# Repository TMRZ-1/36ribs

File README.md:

# 36ribs

Here you will find everything you need to make your own 36ribs keyboard. It's my first project, so it's not too complicated. 

# UPDATE
Added one led under controller to light it a bit in the middle and updated vial software. Added two new cases, with magnets, normal one just without screws in case and second one with integrated plate that need only magnets. From these three my fav is one that have top mounted plate and magnets in case.

Case with screws:

Case with magnets with updated pcb: 

With that layout you will need 36x keycaps(34x 1u keycaps and for spacebars 2x 1.5u keycaps) and 36x switches.

# BOM for pcb
1. 1x pro micro rp2040 controller
2. 36x 1n4148 or 1n4148w diodes, for better looks take through hole diodes
3. 1x B3U-1000P button for reset
4. 1x SK6812 MINI-E RGB
5. Optional. 36x hotswap sockets, pcb have both, solder and hotswap

# BOM for acrylic cover
1. acrylic cover, I've made 3mm for my build
2. 8x m2 10mm standoffs
3. 16x m2 5mm screws

# BOM for v1 case with screws
1. 16x m2 4x3.2 inserts
2. 16x m2 5mm screws

# BOM for case with magnets
1. 8x m2 4x3.2 inserts
2. 8x m2 5mm screws
3. 16x 3x3 cylinder magnets (I used n42)

# BOM for case with magnets and integrated plate
1. 16x 3x3 cylinder magnets (I used n42)

Diodes should be oriented as shown below.

The notched leg of the SK6812 MINI-E RGB LED should be in the marked location

Inserts for v1 case with screws should be embedded in the marked places.

Inserts for magnets case should be embedded in the marked places.

# 36ribs wildlife:

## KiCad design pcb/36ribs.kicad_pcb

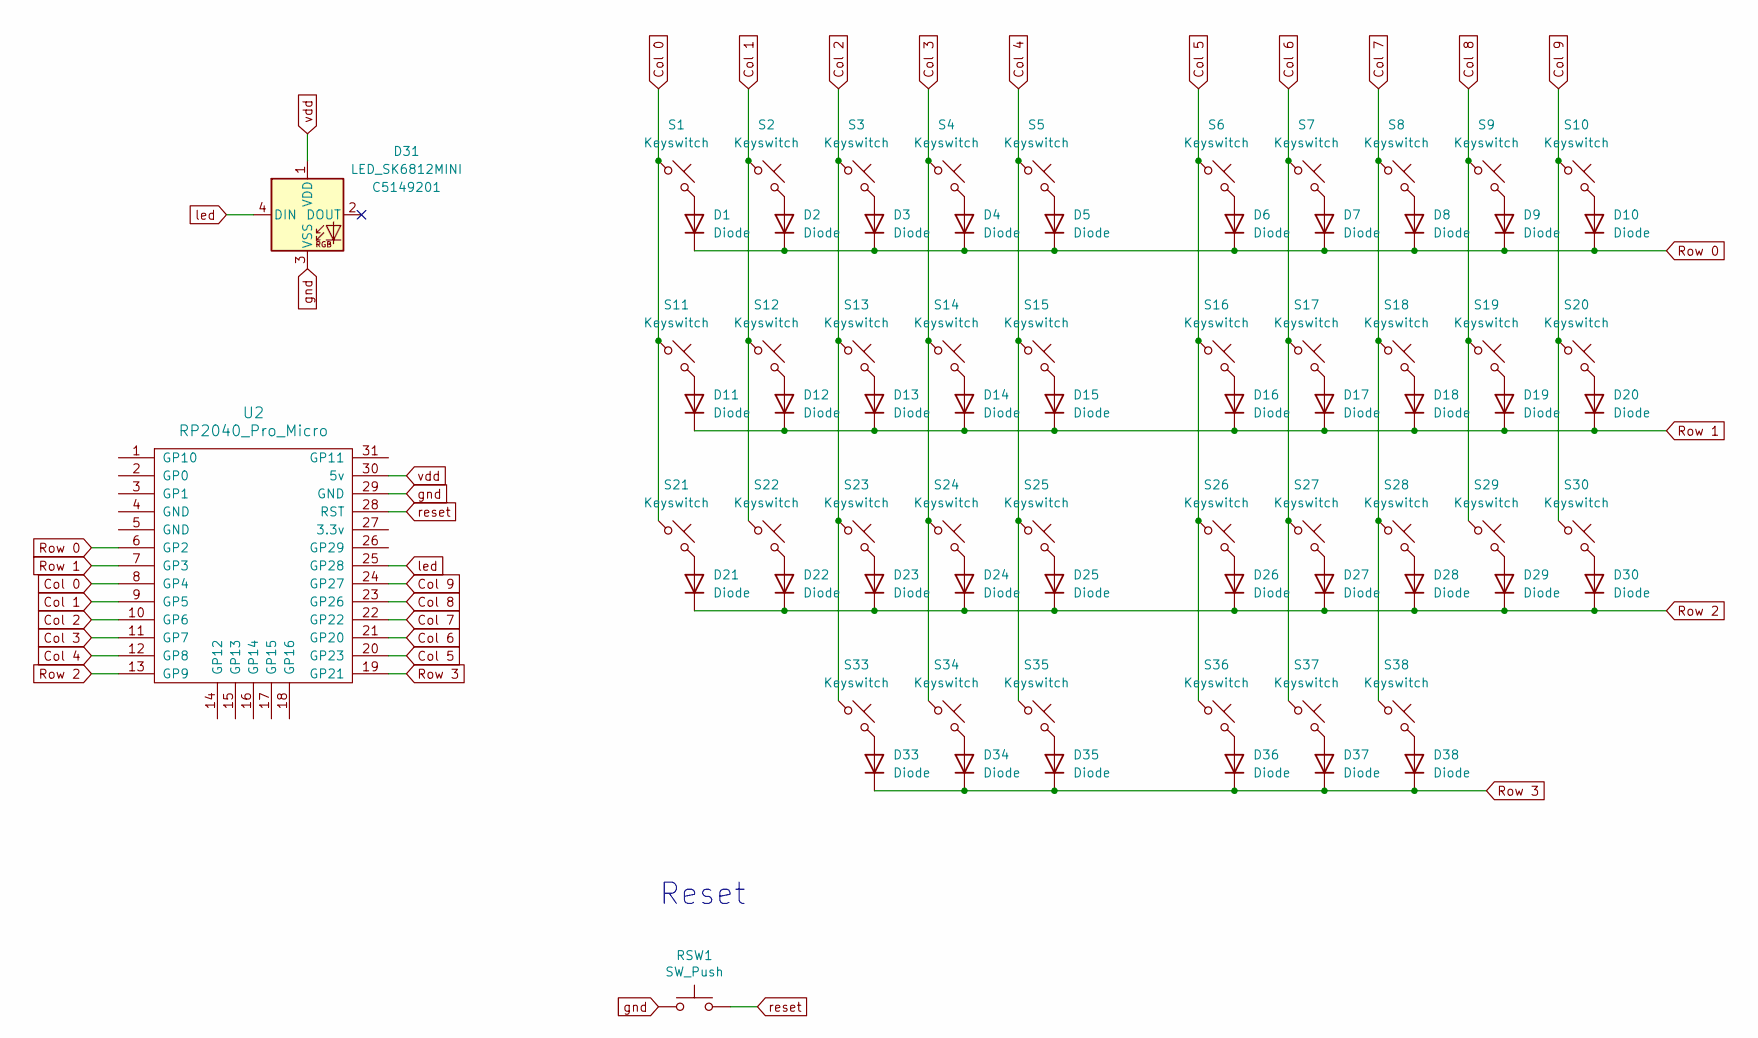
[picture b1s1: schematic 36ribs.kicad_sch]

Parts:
D1, D2, D3, D4, D5, D6, D7, D8, D9, D10, D11, D12, D13, D14, D15, D16, D17, D18, D19, D20, D21, D22, D23, D24, D25, D26, D27, D28, D29, D30, D33, D34, D35, D36, D37, D38: Diode; Diode-dual
D31: LED_SK6812MINI; SK6812-MINI-E; LCSC C5149201
RSW1: SW_Push; SW_SPST_B3U-1000P
S1, S2, S3, S4, S5, S6, S7, S8, S9, S10, S11, S12, S13, S14, S15, S16, S17, S18, S19, S20, S21, S22, S23, S24, S25, S26, S27, S28, S29, S30, S33, S34, S35, S36, S37, S38: Keyswitch; Kailh_socket_MX_optional
U2: RP2040_Pro_Micro

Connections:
Col 0: S1.1, S11.1, S21.1, U2.8 (GP4)
Col 1: S2.1, S12.1, S22.1, U2.9 (GP5)
Col 2: S3.1, S13.1, S23.1, S33.1, U2.10 (GP6)
Col 3: S4.1, S14.1, S24.1, S34.1, U2.11 (GP7)
Col 4: S5.1, S15.1, S25.1, S35.1, U2.12 (GP8)
Col 5: S6.1, S16.1, S26.1, S36.1, U2.20 (GP23)
Col 6: S7.1, S17.1, S27.1, S37.1, U2.21 (GP20)
Col 7: S8.1, S18.1, S28.1, S38.1, U2.22 (GP22)
Col 8: S9.1, S19.1, S29.1, U2.23 (GP26)
Col 9: S10.1, S20.1, S30.1, U2.24 (GP27)
unnamed: D1.2 (A), S1.2
unnamed: D2.2 (A), S2.2
unnamed: D3.2 (A), S3.2
unnamed: D4.2 (A), S4.2
unnamed: D5.2 (A), S5.2
unnamed: D6.2 (A), S6.2
unnamed: D7.2 (A), S7.2
unnamed: D8.2 (A), S8.2
unnamed: D9.2 (A), S9.2
unnamed: D10.2 (A), S10.2
unnamed: D11.2 (A), S11.2
unnamed: D12.2 (A), S12.2
unnamed: D13.2 (A), S13.2
unnamed: D14.2 (A), S14.2
unnamed: D15.2 (A), S15.2
unnamed: D16.2 (A), S16.2
unnamed: D17.2 (A), S17.2
unnamed: D18.2 (A), S18.2
unnamed: D19.2 (A), S19.2
unnamed: D20.2 (A), S20.2
unnamed: D21.2 (A), S21.2
unnamed: D22.2 (A), S22.2
unnamed: D23.2 (A), S23.2
unnamed: D24.2 (A), S24.2
unnamed: D25.2 (A), S25.2
unnamed: D26.2 (A), S26.2
unnamed: D27.2 (A), S27.2
unnamed: D28.2 (A), S28.2
unnamed: D29.2 (A), S29.2
unnamed: D30.2 (A), S30.2
unnamed: D33.2 (A), S33.2
unnamed: D34.2 (A), S34.2
unnamed: D35.2 (A), S35.2
unnamed: D36.2 (A), S36.2
unnamed: D37.2 (A), S37.2
unnamed: D38.2 (A), S38.2
Row 0: D1.1 (K), D2.1 (K), D3.1 (K), D4.1 (K), D5.1 (K), D6.1 (K), D7.1 (K), D8.1 (K), D9.1 (K), D10.1 (K), U2.6 (GP2)
Row 1: D11.1 (K), D12.1 (K), D13.1 (K), D14.1 (K), D15.1 (K), D16.1 (K), D17.1 (K), D18.1 (K), D19.1 (K), D20.1 (K), U2.7 (GP3)
Row 2: D21.1 (K), D22.1 (K), D23.1 (K), D24.1 (K), D25.1 (K), D26.1 (K), D27.1 (K), D28.1 (K), D29.1 (K), D30.1 (K), U2.13 (GP9)
Row 3: D33.1 (K), D34.1 (K), D35.1 (K), D36.1 (K), D37.1 (K), D38.1 (K), U2.19 (GP21)
gnd: D31.3 (VSS), RSW1.1, U2.29 (GND)
led: D31.4 (DIN), U2.25 (GP28)
reset: RSW1.2, U2.28 (RST)
vdd: D31.1 (VDD), U2.30 (5v)

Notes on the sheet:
Reset

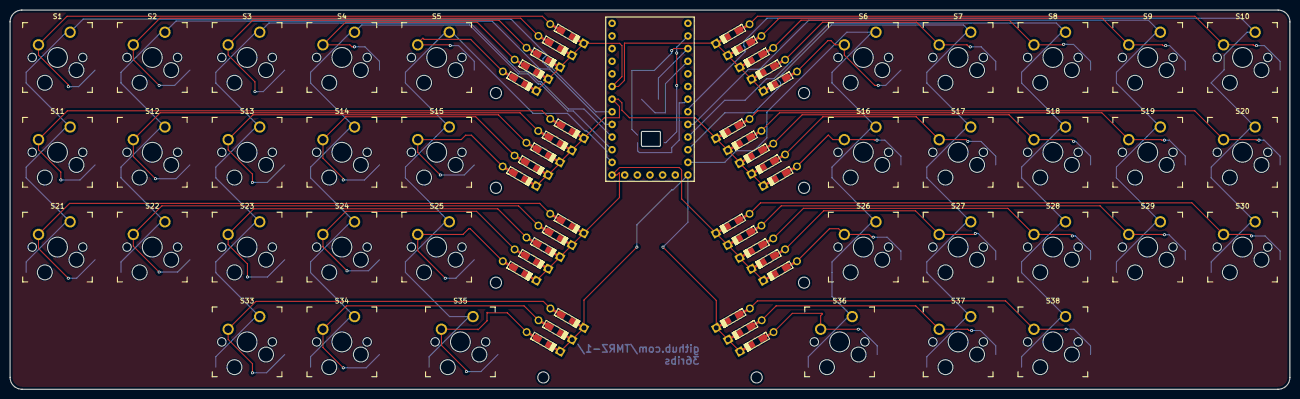
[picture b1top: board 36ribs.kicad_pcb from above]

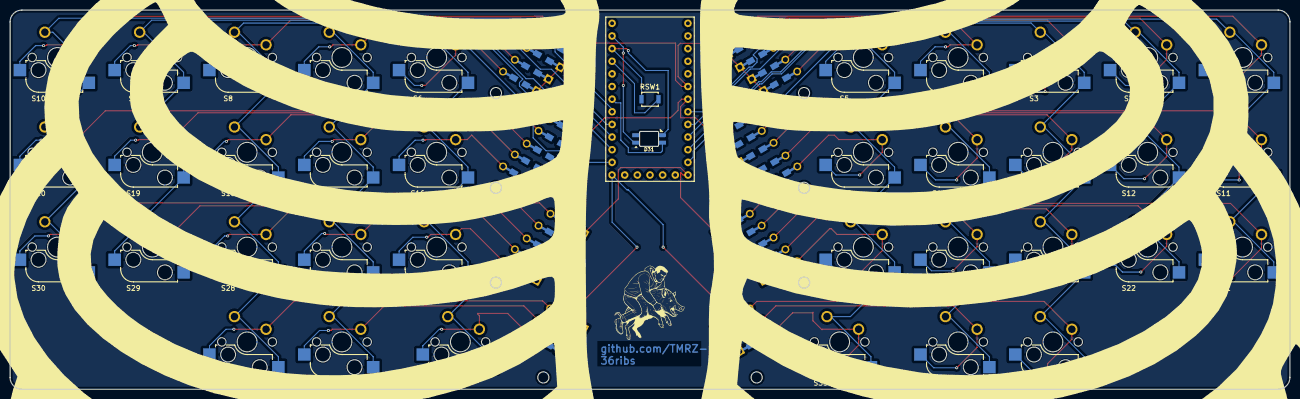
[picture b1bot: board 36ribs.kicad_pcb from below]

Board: 2 copper layers, 257.1 x 76.1 mm, 75 parts (2 on the bottom side), 54 nets.

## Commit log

2025-11-12 Rename test-95.jpg to photos/photo1.jpg
2025-11-12 Rename test-96.jpg to photos/photo-top2
2025-11-12 Rename test-97.jpg to photos/photo-back.jpg
2025-11-12 Revise README for 36ribs keyboard project
    Updated project name and added details about the keyboard.
2025-11-12 Add screenshots to README for visual reference
    Added screenshots to enhance project documentation.
2025-11-12 Fix image paths in README.md
    Updated image paths to use lowercase 'photos' directory.
2025-11-12 Create 1
2025-11-12 Add new firmware file
2025-11-12 Rename pcb/1 to pcb/production_files/1
2025-11-14 Add screenshots to README for visual reference
2025-11-14 Rename 36ribs diode.png to 36ribs-diode.png
2025-11-14 Rename 36ribs inserts.png to 36ribs-inserts.png
2025-11-14 Update README.md
    Updated images and added orientation instructions for diodes and inserts.
2025-11-14 Update README.md
    Updated project description for clarity and detail.
2025-11-14 Update README.md
    Updated keycap and switch requirements for clarity.
2026-02-04 Addimages to README
2026-02-04 Add images to README
2026-06-26 Update README.md
    Updated the README to improve formatting and added new BOM sections.
2026-06-26 Update README with case images and BOM changes
    Added images of the keyboard case and updated BOM items.
2026-06-26 Update README.md
    Added update section and improved image formatting.
2026-06-26 Create a
2026-06-26 Create sa
2026-06-26 Rename keymap.c to q
